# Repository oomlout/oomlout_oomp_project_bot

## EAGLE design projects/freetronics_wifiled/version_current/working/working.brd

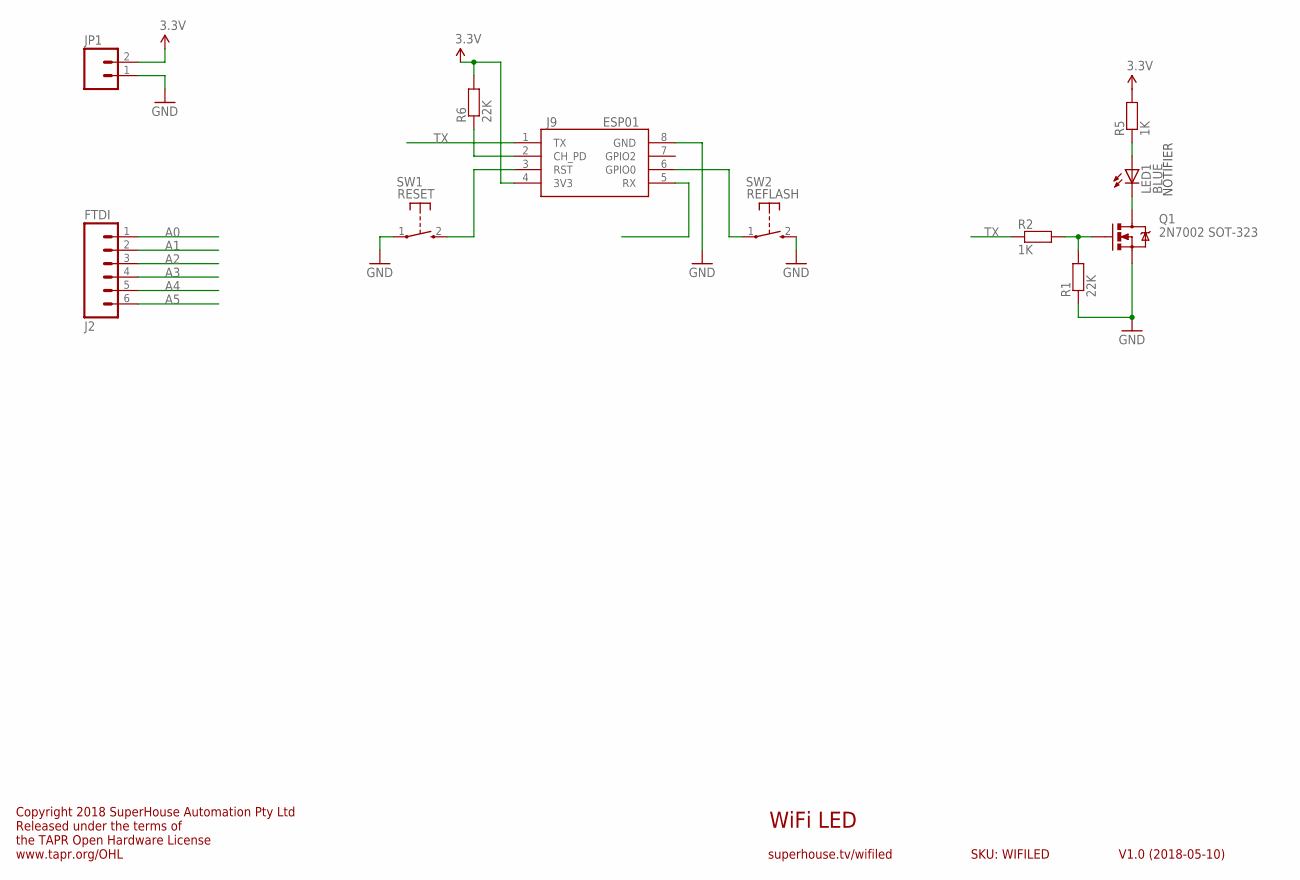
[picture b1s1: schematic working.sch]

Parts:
J2: FTDI; 1X06
J9: ESP01
JP1: M02PTH; 1X02
LED1: BLUE; LED-0603
Q1: 2N7002 SOT-323; SOT32-3
R1, R6: 22K; 0603
R2, R5: 1K; 0603
SW1: RESET; TACTILE_SWITCH_SMD_2PIN_TINY
SW2: REFLASH; TACTILE_SWITCH_SMD_2PIN_TINY

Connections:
3.3V: J9.4 (3V3), JP1.2, R5.2, R6.2
A0: J2.1
A1: J2.2
A2: J2.3
A3: J2.4
A4: J2.5
A5: J2.6
GND: J9.8 (GND), JP1.1, Q1.2 (S), R1.1, SW1.1, SW2.2 (S)
unnamed: J9.6 (GPIO0), SW2.1
unnamed: LED1.C, Q1.3 (D)
unnamed: J9.3 (RST), SW1.2 (S)
unnamed: J9.2 (CH_PD), R6.1
unnamed: LED1.A, R5.1
unnamed: Q1.1 (G), R1.2, R2.2
TX: J9.1 (TX), R2.1

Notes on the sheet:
WiFi LED
V1.0 (2018-05-10)
superhouse.tv/wifiled
SKU: WIFILED
Copyright 2018 SuperHouse Automation Pty Ltd Released under the terms of the TAPR Open Hardware License www.tapr.org/OHL
NOTIFIER

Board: 2 copper layers, 11 parts (0 on the bottom side), 9 nets, no tracks yet.

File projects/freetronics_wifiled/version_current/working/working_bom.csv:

"Id";"Designator";"Footprint";"Quantity";"Designation";"Supplier and ref";
1;"R1,R6";"0603";2;"22K";;;
2;"SW2";"TACTILE_SWITCH_SMD_2PIN_TINY";1;"REFLASH";;;
3;"LED1";"LED-0603";1;"BLUE";;;
4;"J9";"ESP01";1;"ESP01";;;
5;"R2,R5";"0603";2;"1K";;;
6;"J2";"1X06";1;"FTDI";;;
7;"SW1";"TACTILE_SWITCH_SMD_2PIN_TINY";1;"RESET";;;
8;"Q1";"SOT32-3";1;"2N7002 SOT-323";;;
9;"JP1";"1X02";1;"";;;

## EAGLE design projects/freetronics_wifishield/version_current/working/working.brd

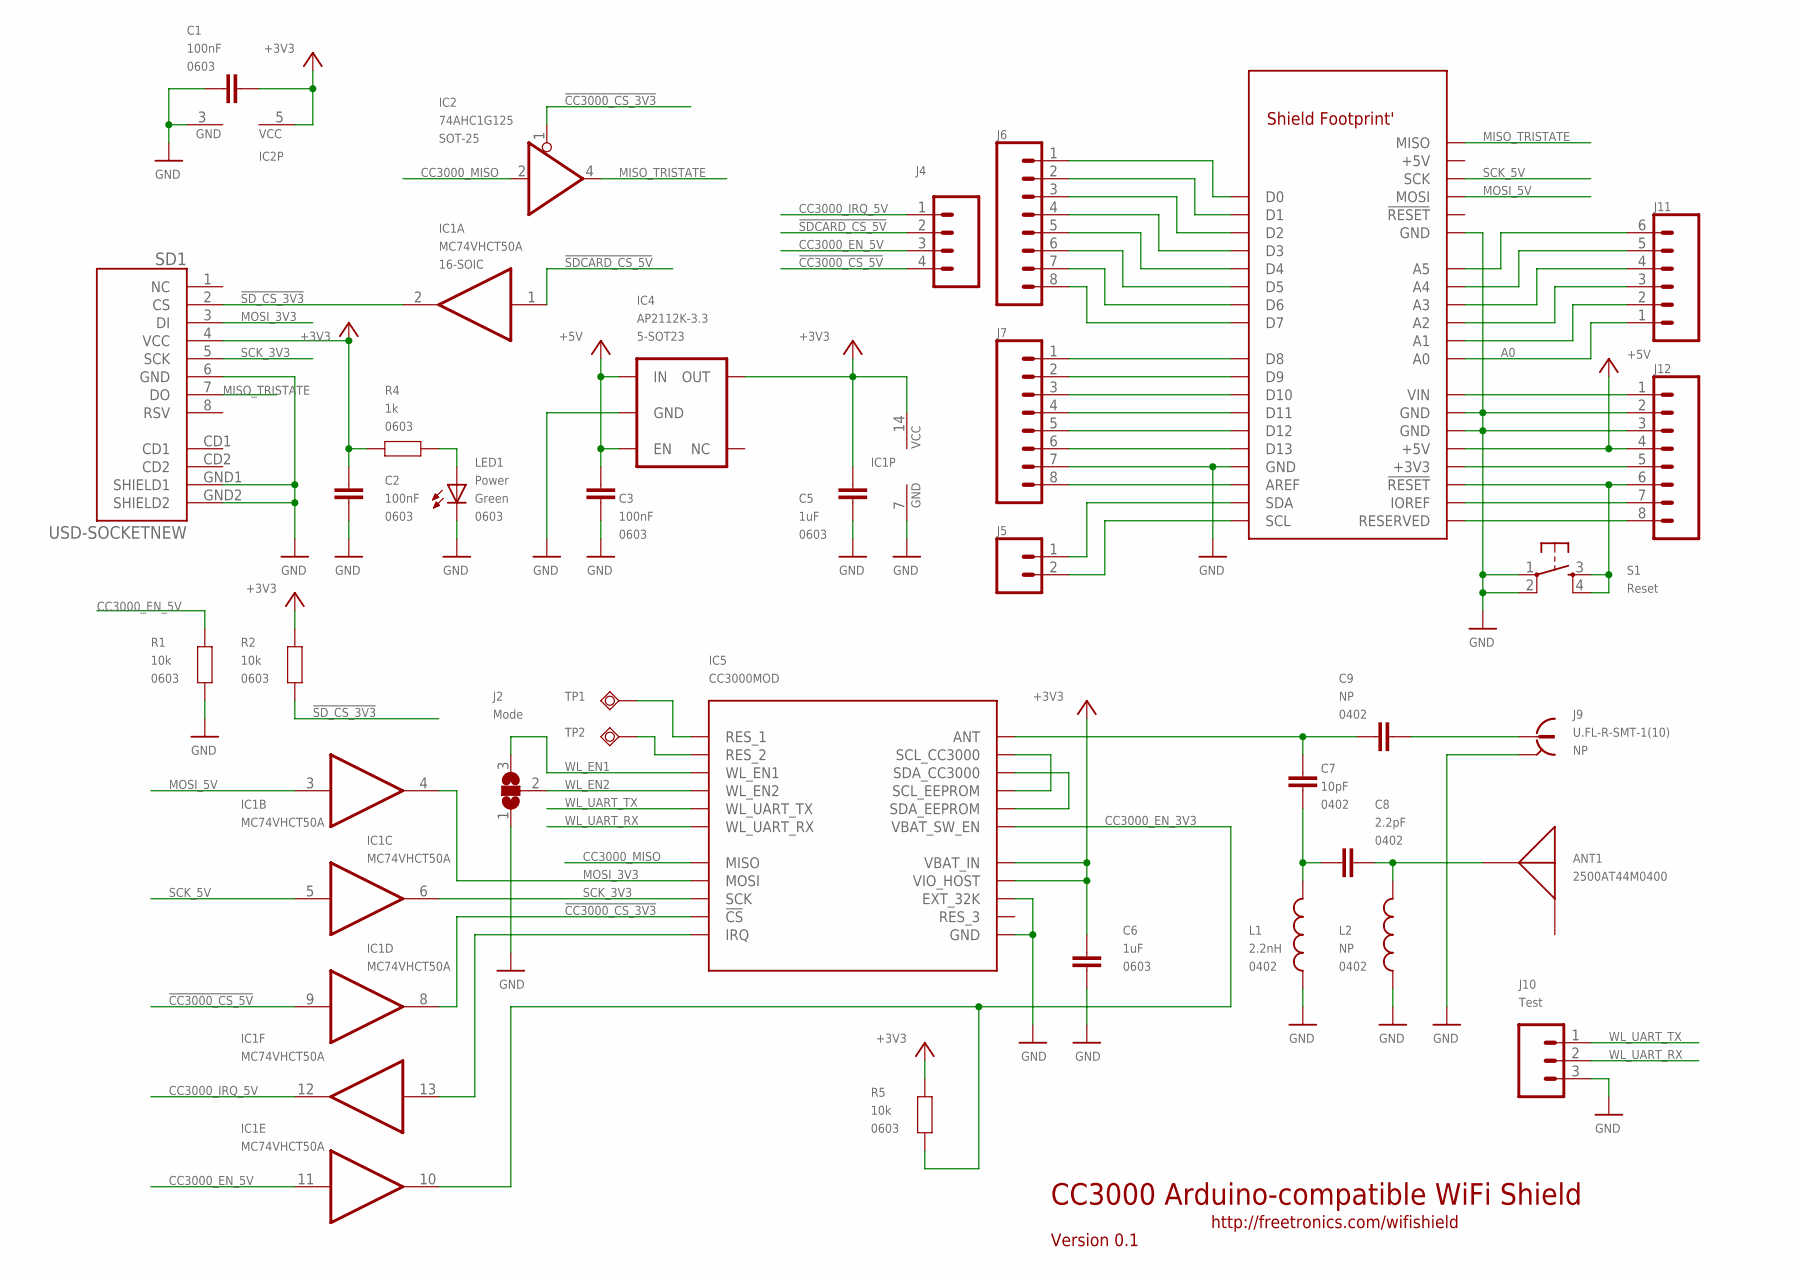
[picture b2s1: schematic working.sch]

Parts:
ANT1: 2500AT44M0400
C1, C2, C3: 100nF; 0603
C5, C6: 1uF; 0603
C7: 10pF; C0402
C8: 2.2pF; C0402
C9: NP; C0402
IC1: MC74VHCT50A; SO14
IC2: 74AHC1G125; SOT23-5
IC4: AP2112K-3.3; SOT23-5
IC5: CC3000MOD; CC3000
J2: Mode; SJ_2
J4: M04PTH; 1X04
J5: M02PTH; 1X02
J6, J7, J12: M08STD; 1X08
J8: ARDUINO-SHIELD_R3; ARDUINO-SHIELD_R3_NOHOLES
J9: U.FL-R-SMT-1(10); UFL
J10: Test; 1X03
J11: M06SIP; 1X06
L1: 2.2nH; C0402
L2: NP; C0402
LED1: Power; LED-0603
R1, R2, R5: 10k; 0603
R4: 1k; 0603
S1: Reset; TACTILE_SWITCH_SMD
SD1: USD-SOCKETNEW; MICRO-SD-SOCKET-PP
TP1: R1; TP06R
TP2: R2; TP06R

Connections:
!CC3000_CS_3V3: IC1.8 (O), IC2.1 (OE), IC5.12 (!CS)
!CC3000_CS_5V: IC1.9 (I), J4.4
!SDCARD_CS_5V: IC1.1 (I), J4.2
!SD_CS_3V3: IC1.2 (O), R2.2, SD1.2 (CS)
+3V3: C1.2, C2.1, C5.1, C6.2, IC1.14 (VCC), IC2.5 (VCC), IC4.5 (OUT), IC5.19 (VBAT_IN), IC5.23 (VIO_HOST), R2.1, R4.2, R5.1, SD1.4 (VCC)
+5V: C3.2, IC4.1 (IN), IC4.3 (EN), J8.+5V, J12.4
A0: J8.A0, J11.1
CC3000_EN_3V3: IC1.10 (O), IC5.26 (VBAT_SW_EN), R5.2
CC3000_EN_5V: IC1.11 (I), J4.3, R1.1
CC3000_IRQ_5V: IC1.12 (O), J4.1
CC3000_MISO: IC2.2 (I), IC5.13 (MISO)
GND: C1.1, C2.2, C3.1, C5.2, C6.1, IC1.7 (GND), IC2.3 (GND), IC4.2 (GND), IC5.1 (GND), IC5.9 (GND), IC5.10 (GND), IC5.11 (GND), IC5.16 (GND), IC5.18 (GND), IC5.20 (GND), IC5.21 (EXT_32K), IC5.22 (GND), IC5.25 (GND), IC5.31 (GND), IC5.32 (GND), IC5.33 (GND), IC5.34 (GND), IC5.36 (GND), IC5.37 (GND), IC5.38 (GND), IC5.39 (GND), IC5.40 (GND), IC5.41 (GND), IC5.42 (GND), IC5.43 (GND), IC5.44 (GND), IC5.45 (GND), IC5.46 (GND), J2.1, J7.7, J8.GND, J8.GND@0 (GND), J8.GND@1 (GND), J8.GND@2 (GND), J9.GND, J9.GND@1 (GND), J10.3, J12.2, J12.3, L1.2, L2.2, LED1.C, R1.2, S1.1, S1.2, SD1.6 (GND), SD1.GND1 (SHIELD1), SD1.GND2 (SHIELD2)
IOREF: J8.IOREF, J12.7
MISO_TRISTATE: IC2.4 (O), J8.MISO, SD1.7 (DO)
MOSI_3V3: IC1.4 (O), IC5.15 (MOSI), SD1.3 (DI)
MOSI_5V: IC1.3 (I), J8.MOSI
unnamed: IC5.27 (SDA_EEPROM), IC5.28 (SDA_CC3000)
unnamed: IC5.29 (SCL_EEPROM), IC5.30 (SCL_CC3000)
unnamed: LED1.A, R4.1
unnamed: C7.2, C9.2, IC5.35 (ANT)
unnamed: IC5.4 (RES_2), TP2.TP
unnamed: IC5.2 (RES_1), TP1.TP
unnamed: C9.1, J9.SIG
unnamed: IC1.13 (I), IC5.14 (IRQ)
unnamed: J8.A1, J11.2
unnamed: J8.A2, J11.3
unnamed: J8.A3, J11.4
unnamed: J8.A4, J11.5
unnamed: J8.A5, J11.6
unnamed: J8.RESERVED, J12.8
unnamed: J8.VIN, J12.1
unnamed: J8.3V3 (+3V3), J12.5
unnamed: J8.!RESET, J12.6, S1.3, S1.4
unnamed: J6.1, J8.D0
unnamed: J6.2, J8.D1
unnamed: J6.3, J8.D2
unnamed: J6.4, J8.D3
unnamed: J6.5, J8.D4
unnamed: C7.1, C8.2, L1.1
unnamed: ANT1.P$1, C8.1, L2.1
unnamed: J6.6, J8.D5
unnamed: J6.7, J8.D6
unnamed: J6.8, J8.D7
unnamed: J5.1, J8.SDA
unnamed: J7.8, J8.AREF
unnamed: J7.6, J8.D13
unnamed: J7.5, J8.D12
unnamed: J5.2, J8.SCL
unnamed: J7.1, J8.D8
unnamed: J7.2, J8.D9
unnamed: J7.3, J8.D10
unnamed: J7.4, J8.D11
SCK_3V3: IC1.6 (O), IC5.17 (SCK), SD1.5 (SCK)
SCK_5V: IC1.5 (I), J8.SCK
WL_EN1: IC5.7 (WL_EN1), J2.3
WL_EN2: IC5.5 (WL_EN2), J2.2
WL_UART_RX: IC5.8 (WL_UART_RX), J10.2
WL_UART_TX: IC5.6 (WL_UART_TX), J10.1

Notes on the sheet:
CC3000 Arduino-compatible WiFi Shield
Version 0.1
http://freetronics.com/wifishield

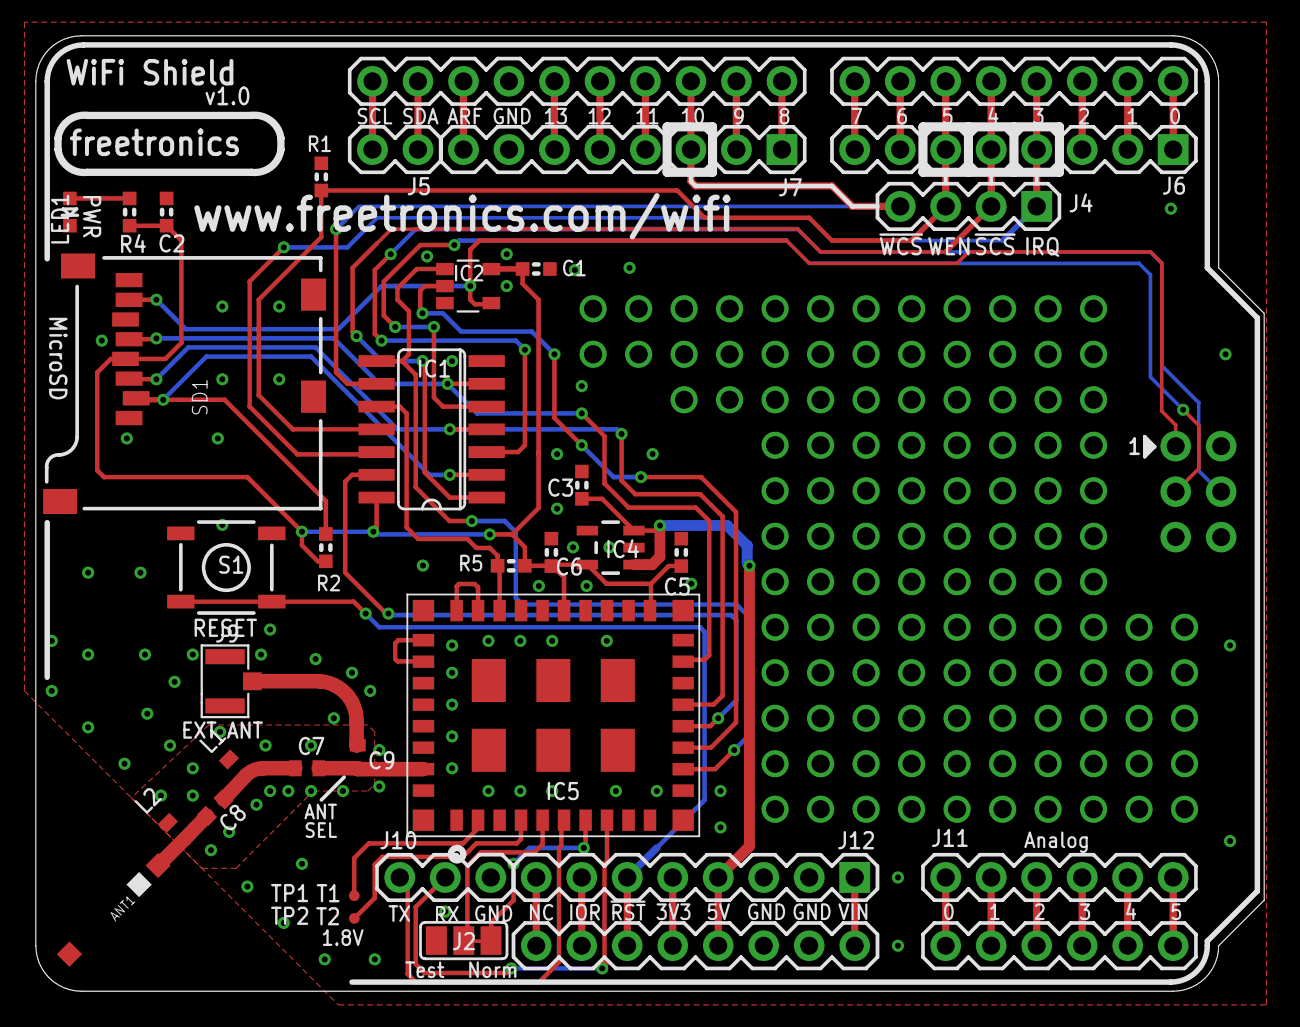
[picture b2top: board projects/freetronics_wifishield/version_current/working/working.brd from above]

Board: 2 copper layers, 68.6 x 53.3 mm, 34 parts (0 on the bottom side), 58 nets.

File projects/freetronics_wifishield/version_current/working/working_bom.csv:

"Id";"Designator";"Footprint";"Quantity";"Designation";"Supplier and ref";
1;"J11";"1X06";1;"";;;
2;"L2,C9";"C0402";2;"NP";;;
3;"J12,J6,J7";"1X08";3;"";;;
4;"C3,C2,C1";"0603";3;"100nF";;;
5;"R1,R2,R5";"0603";3;"10k";;;
6;"C5,C6";"0603";2;"1uF";;;
7;"S1";"TACTILE_SWITCH_SMD";1;"Reset";;;
8;"C8";"C0402";1;"2.2pF";;;
9;"J2";"SJ_2";1;"Mode";;;
10;"J10";"1X03";1;"Test";;;
11;"LED1";"LED-0603";1;"Power";;;
12;"J8";"ARDUINO-SHIELD_R3_NOHOLES";1;"ARDUINO-SHIELD_R3";;;
13;"R4";"0603";1;"1k";;;
14;"C7";"C0402";1;"10pF";;;
15;"J5";"1X02";1;"";;;
16;"J4";"1X04";1;"";;;
17;"L1";"C0402";1;"2.2nH";;;
18;"IC4";"SOT23-5";1;"AP2112K-3.3";;;
19;"SD1";"MICRO-SD-SOCKET-PP";1;"USD-SOCKETNEW";;;
20;"TP1";"TP06R";1;"R1";;;
21;"IC1";"SO14";1;"MC74VHCT50A";;;
22;"IC2";"SOT23-5";1;"74AHC1G125";;;
23;"IC5";"CC3000";1;"CC3000MOD";;;
24;"TP2";"TP06R";1;"R2";;;
25;"J9";"UFL";1;"U.FL-R-SMT-1(10)";;;
26;"ANT1";"2500AT44M0400";1;"2500AT44M0400";;;

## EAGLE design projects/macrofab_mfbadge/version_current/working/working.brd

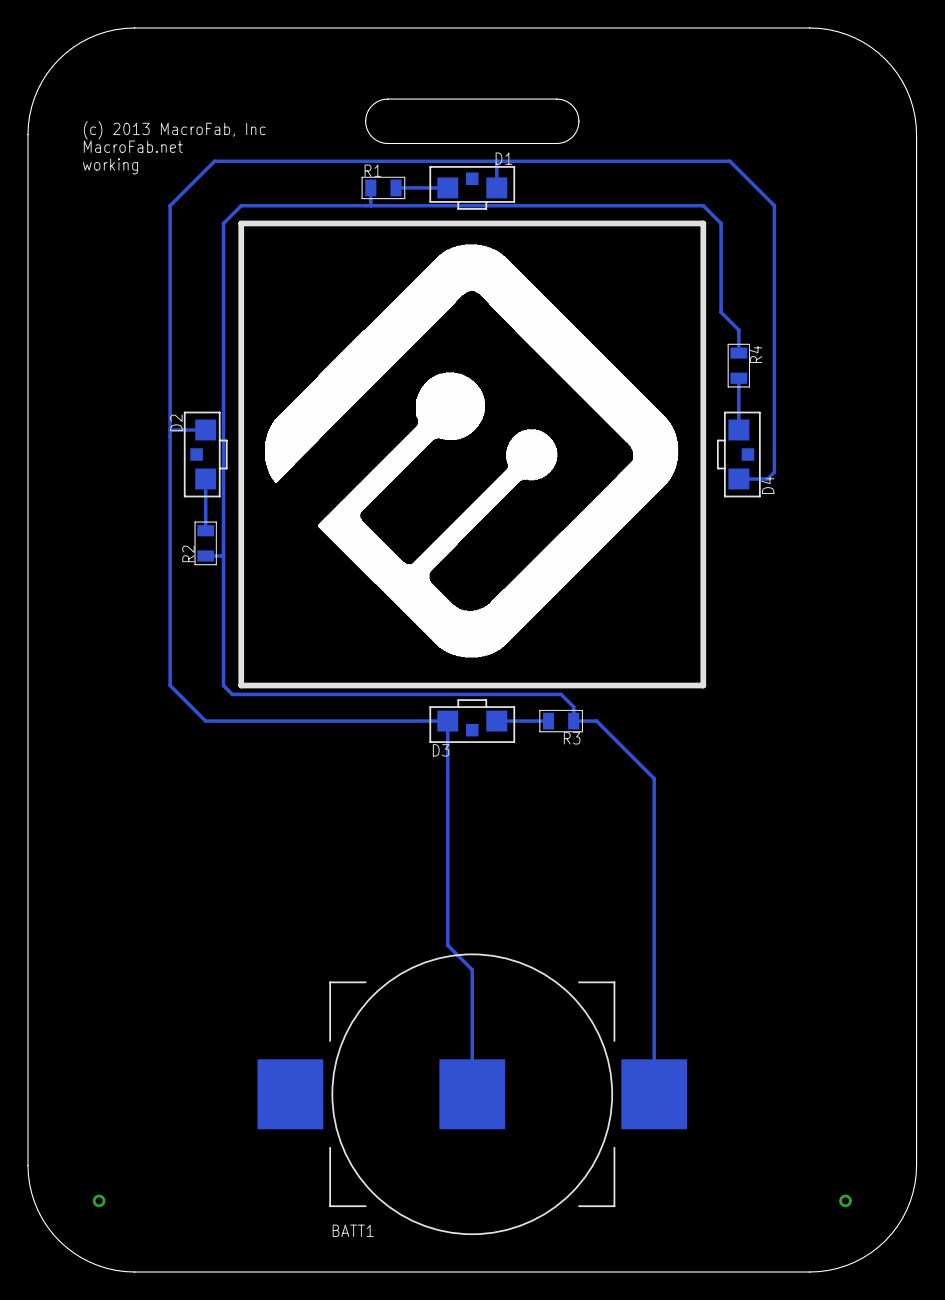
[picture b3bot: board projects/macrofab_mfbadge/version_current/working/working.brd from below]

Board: 2 copper layers, 63.5 x 88.9 mm, 10 parts (10 on the bottom side), 6 nets.

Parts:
BATT1: SMTM2032.TR; SMTM2032
D1, D2, D3, D4: APA3010SURCK; APA3010
R1, R2, R3, R4: 100; 0805
U$1: MF_FRAMEMF_FRAME; MF_FRAME

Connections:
3V: BATT1.BATT+_0, BATT1.BATT+_1, R1.1, R2.1, R3.1, R4.1
GND: BATT1.BATT-, D1.1, D2.1, D3.1, D4.1
unnamed: D1.2, R1.2
unnamed: D2.2, R2.2
unnamed: D3.2, R3.2
unnamed: D4.2, R4.2

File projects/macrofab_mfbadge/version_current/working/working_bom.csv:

"Id";"Designator";"Footprint";"Quantity";"Designation";"Supplier and ref";
1;"D2,D3,D1,D4";"APA3010";4;"APA3010SURCK";;;
2;"R1,R4,R3,R2";"0805";4;"100";;;
3;"U$1";"MF_FRAME";1;"MF_FRAMEMF_FRAME";;;
4;"BATT1";"SMTM2032";1;"SMTM2032.TR";;;

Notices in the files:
projects/freetronics_wifishield/version_current/working/working.brd:
(C) 2014 Freetronics Pty Ltd
Licensed under TAPR
Open Hardware License
parts and their libraries:
PP_Aesthetics: (c) 2013 MacroFab, Inc
